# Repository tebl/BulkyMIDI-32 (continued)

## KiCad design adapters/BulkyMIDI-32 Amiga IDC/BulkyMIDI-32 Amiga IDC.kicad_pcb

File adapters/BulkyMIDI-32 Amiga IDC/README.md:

# BulkyMIDI-32 Amiga (IDC)
The Commodore Amiga didn't come with built-in MIDI-ports. Yes, Atari ST fans we get it now. MIDI ports are kind of awesome now when you own a real Roland MT-32, BulkyMIDI-32 or just about any other version of [mt32-pi](https://github.com/dwhinham/mt32-pi). This adapter is meant so that you'd have some way of connecting your favourite MIDI-device to your favourite Commodore Amiga computer (as long as it one of the more common variants and within reason). 

This adapter plugs into the serial port of your Commodore Amiga 500/600/1200/2000/3000/4000, adding the ports you never knew you wanted. This version of the adapter has an IDC-plug on it, allowing it to be used with a 26-pin IDC to female DB25 cable that can be bought pre-made. If you want one that directly plugs into the serial port without a cable between the two, check out [BulkyMIDI-32 Amiga](https://github.com/tebl/BulkyMIDI-32/tree/main/adapters/BulkyMIDI-32%20Amiga) instead.

- [1> Building the device](#1-building-the-device)
- [2> Schematic](#2-schematic)
- [3> BOM](#3-bom)

# 1> Building the device
Building the device should be a straight-forward affair, you just solder the meager selection of components into place. Pay attention to keep the alignment of the parts somewhat straight, then you should be good. This documentation was written with a board that looks like the following in mind, but note that the github-repository may contain changes that have yet to be tested (therefore, it is recommend that PCBs are ordered using PCBWay links listed in the BOM).

Resistors have here been added to the board. Do however note the presence of the single 1n4148-diode, this needs to be soldered in with the black stripe as indicated on the PCB itself. I've also added IC sockets, simply because I was able to afford the option of stealing the ICs that go into them at a later point in time.

The 100nF capacitors have been added to the board, all of these are of the same value. The five around the MAX232**A** are also 100nF, this means that we actually need to use a MAX232**A** version of the chip - the cheaper MAX232**CPE** commonly encountered on sites such as Ebay and AliExpress will not function as it is, so ensure that you purchase the correct chip. The 7805 is soldered flush against the board, this supplies power to the ICs on the board.

The 26-pin IDC-connector was soldered to the board. While you could just use standard pin-headers here instead, I prefer to use these as you get keying to ensure the cable isn't inserted the wrong way around. I didn't have enough 5-pin DIN connectors so what you see is what I've got.

Here the cable has been added, but while you can purchase these ready-made I prefer purchasing a cable with 26-pin IDC-connectors on both ends and just cutting them into two pieces for use with various projects at a later point. The Amiga computers mentioned earlier require a female DB25, so what I've done is aligned a *DB25 IDC flat ribbon* connector to the end of one of the IDC-cables (note that one strand on the end has been removed). There are dedicated tools for attiching this kind of plug, but I prefer to just put them on a hard surface and jam them into place with the handle of a screwdriver between it and the back of my hand - loop the cable back over, then attach the strain-relief clip to the top.

# 2> Schematic
The supplied KiCad files should be sufficient as both a schematic and as a  starting point for ordering PCBs (basically you could just zip the contents of the export folder and upload that on a fabrication site), the schematic is also available in [PDF-format](https://github.com/tebl/BulkyMIDI-32/tree/main/documentation/schematic/adapters) and this is what you'll need to print and work your way through when things fail to work as expected.

# 3> BOM
Most parts should be easy to get a hold of from your favourite local electronic component shop, but given that I don't have access to such shops where I live so everything was based on whatever I could get cheapest from eBay/AliExpress (free shipping, but plan on waiting 3-4 weeks for delivery). As I expect that most will build this adapter solely for MIDI-output, the values required for the MIDI input have been listed in parenthesis.

| Reference      | Item                                                  | Count | Order  |
| ---------------| ----------------------------------------------------- | ----- | ------ |
| Faceplate PCB  | Fabricate using Gerber files                          |     1 | [PCBWay](https://www.pcbway.com/project/shareproject/Amiga_MIDI_Interface_IDC_81756c6e.html)
| C1-C9          | 100nF ceramic capacitor (5mm)                         |     9 |
| D1             | 1N4148N small signal diode (DO-35)                    |    (1)|
| J1             | 2x13 pin straight IDC socket                          |     1 |
| J2             | Female S-terminal 5pin DIN PCB                        |     1 |
| J3             | Female S-terminal 5pin DIN PCB                        |    (1)|
| R1             | 2k2 (2200) ohm resistor                               |     1 |
| R2,R3          | 220 ohm resistor                                      |     2 |
| R4             | 220 ohm resistor                                      |    (1)|
| U1             | 6N138 opto-coupler (DIP-8)                            |    (1)|
| U2             | 7805 (TO-220)                                         |     1 |
| U3             | 74HCT00 (DIP-14)                                      |     1 |
| U4             | MAX232A (DIP-16)                                      |     1 |

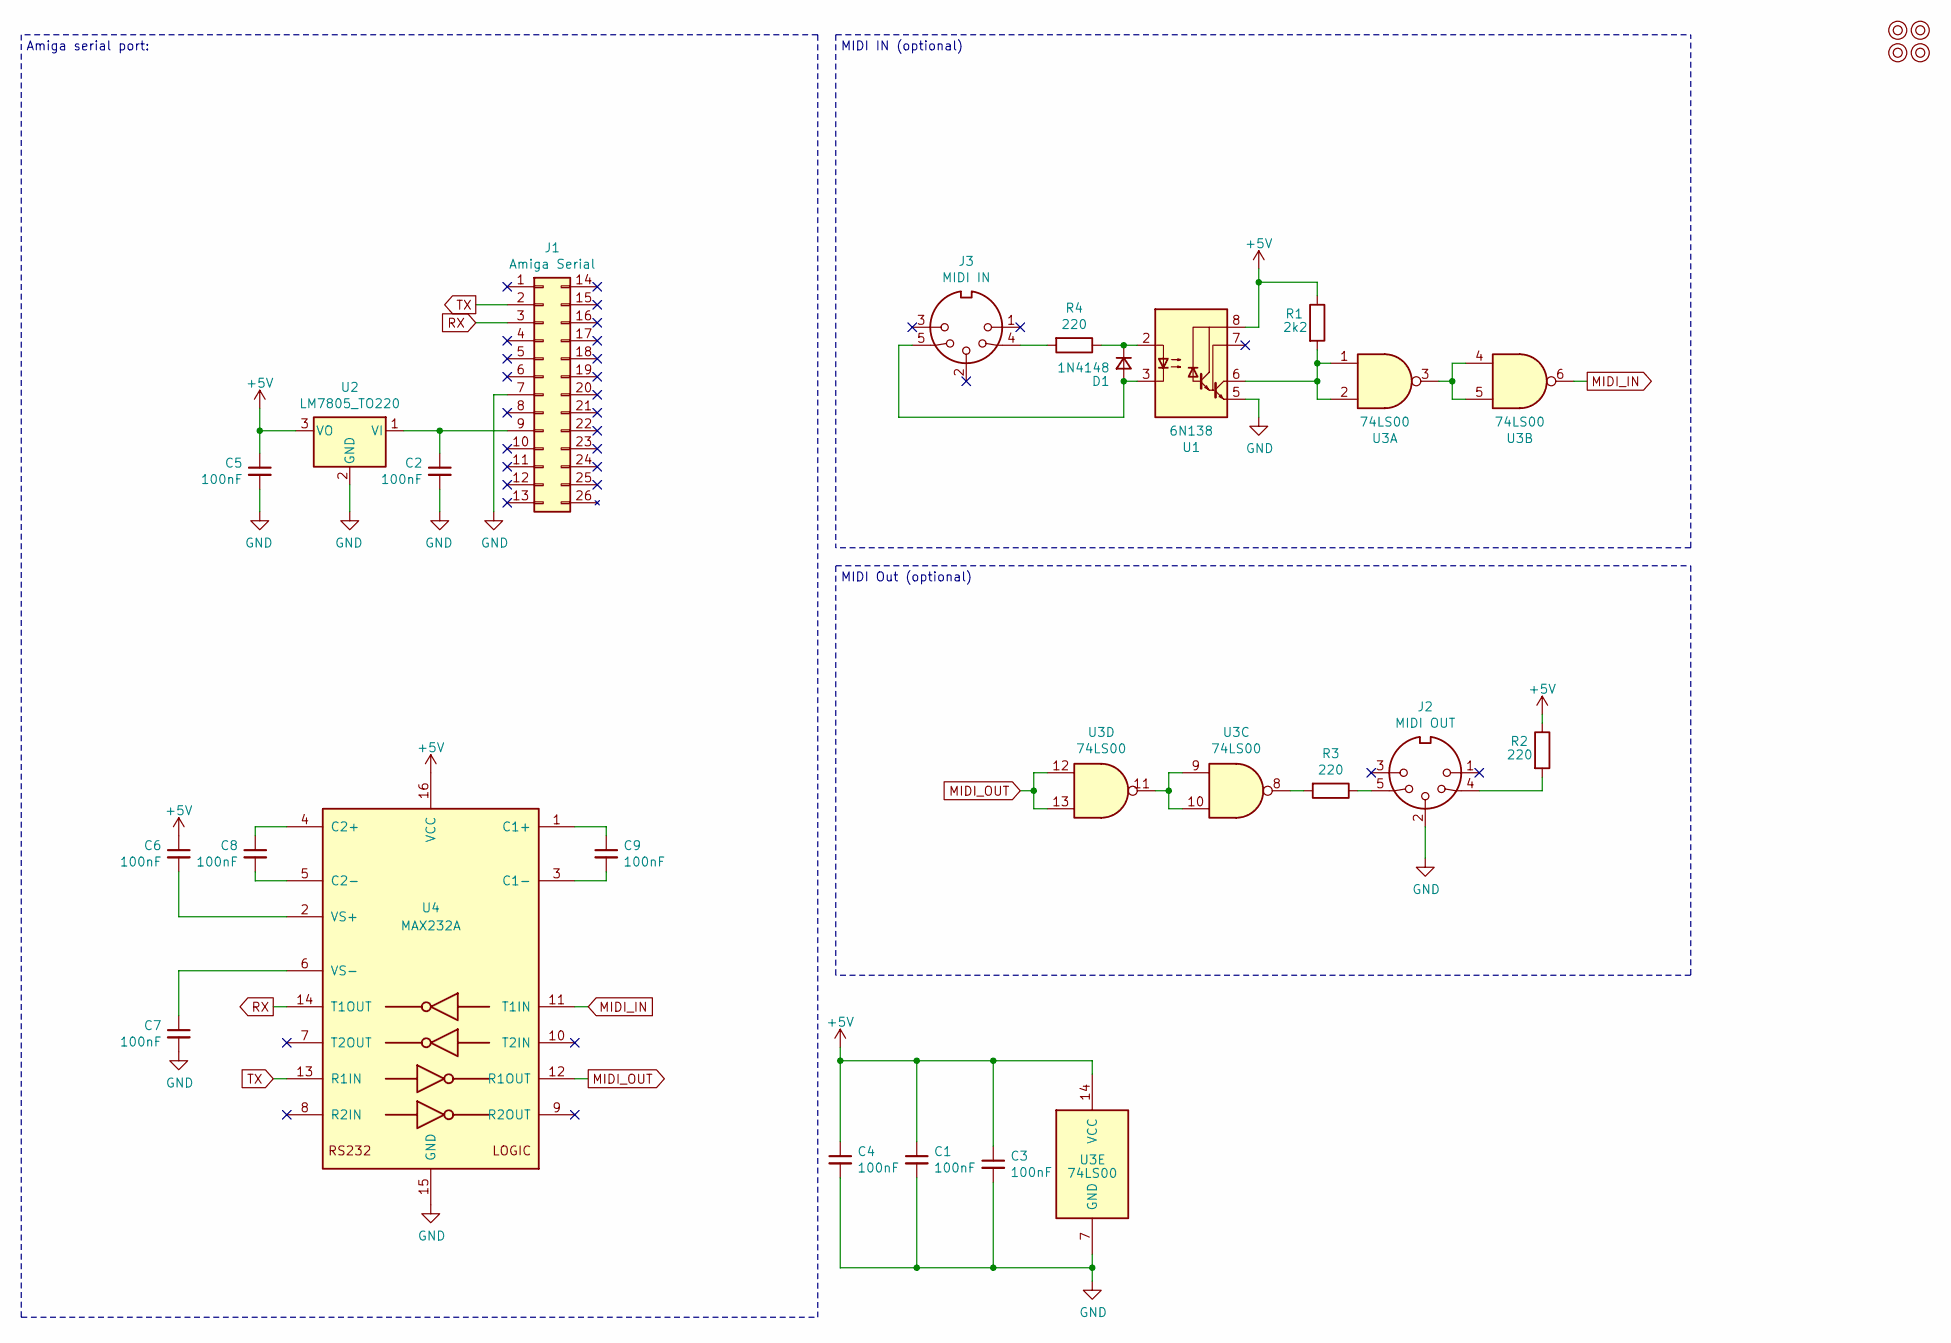
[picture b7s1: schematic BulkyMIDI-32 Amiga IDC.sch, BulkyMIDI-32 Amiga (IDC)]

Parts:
C1, C2, C3, C4, C5, C6, C7, C8, C9: 100nF; C_Disc_D4.7mm_W2.5mm_P5.00mm
D1: 1N4148; D_DO-35_SOD27_P7.62mm_Horizontal
J1: Amiga Serial; DB25_Serial_IDC
J2: MIDI OUT; DIN5_MIDI
J3: MIDI IN; DIN5_MIDI
M1, M2, M3, M4: Mounting; M3
R1: 2k2; R_Axial_DIN0207_L6.3mm_D2.5mm_P10.16mm_Horizontal
R2, R3, R4: 220; R_Axial_DIN0207_L6.3mm_D2.5mm_P10.16mm_Horizontal
U1: 6N138; DIP-8_W7.62mm_Socket_LongPads
U2: LM7805_TO220; TO-220-3_Horizontal_TabDown
U3: 74LS00; DIP-14_W7.62mm_Socket_LongPads
U4: MAX232A; DIP-16_W7.62mm_Socket_LongPads

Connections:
+5V: C1.1, C3.1, C4.1, C5.1, C6.1, R1.1, R2.1, U1.8 (VCC), U2.3 (VO), U3.14 (VCC), U4.16 (VCC)
GND: C1.2, C2.2, C3.2, C4.2, C5.2, C7.2, J1.7 (GND), J2.2, U1.5 (GND), U2.2 (GND), U3.7 (GND), U4.15 (GND)
MIDI_IN: U3.6, U4.11 (T1IN)
MIDI_OUT: U3.12, U3.13, U4.12 (R1OUT)
unnamed: C2.1, J1.9 (VDD), U2.1 (VI)
unnamed: C6.2, U4.2 (VS+)
unnamed: C7.1, U4.6 (VS-)
unnamed: C8.1, U4.4 (C2+)
unnamed: C8.2, U4.5 (C2-)
unnamed: C9.1, U4.1 (C1+)
unnamed: C9.2, U4.3 (C1-)
unnamed: D1.1 (K), R4.1, U1.2 (C1)
unnamed: D1.2 (A), J3.5, U1.3 (C2)
unnamed: J2.4, R2.2
unnamed: J2.5, R3.1
unnamed: J3.4, R4.2
unnamed: R1.2, U1.6 (VO2), U3.1, U3.2
unnamed: R3.2, U3.8
unnamed: U3.3, U3.4, U3.5
unnamed: U3.9, U3.10, U3.11
RX: J1.3 (RX), U4.14 (T1OUT)
TX: J1.2 (TX), U4.13 (R1IN)

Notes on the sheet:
MIDI IN (optional)
MIDI Out (optional)
Amiga serial port:

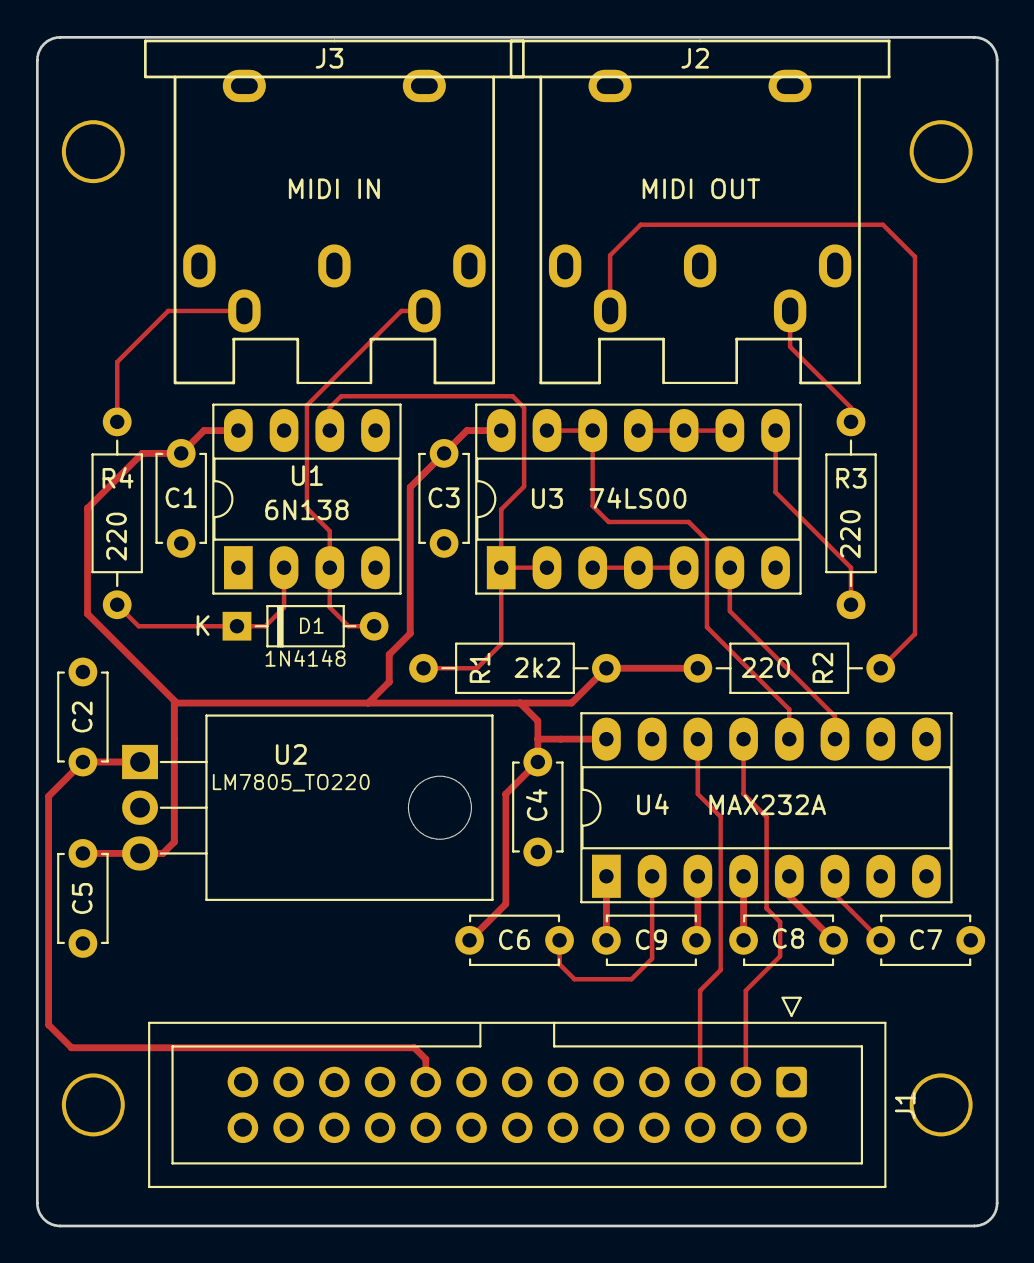
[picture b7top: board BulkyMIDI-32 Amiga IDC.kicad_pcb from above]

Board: 2 copper layers, 53.3 x 66.0 mm, 25 parts (0 on the bottom side), 22 nets.
